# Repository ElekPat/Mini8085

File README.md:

This is my Kicad version of http://www.malinov.com/Home/sergeys-projects/minimax8085, I called it V1.1.

MAX232 and DS1210 have been removed.
Added a 6 pin header for FTDI like external USB to serial adapter.

A prototype 2.54mm pitch zone was created (pads only on bottom face). You can see it populated here with a PIC16 acting as an I2C Master controller for the 8085 (requires changes to the original MiniMax8085 GAL).

For assembling source files, I use http://john.ccac.rwth-aachen.de:8000/as/ (Macro Assembler compatible with multiple target CPUs, see my other projects)

Use the following 2 command lines to generate a HEX file:
 - asw.exe -cpu 8085 -L source.asm
 - p2hex.exe source.p -k -F Intel

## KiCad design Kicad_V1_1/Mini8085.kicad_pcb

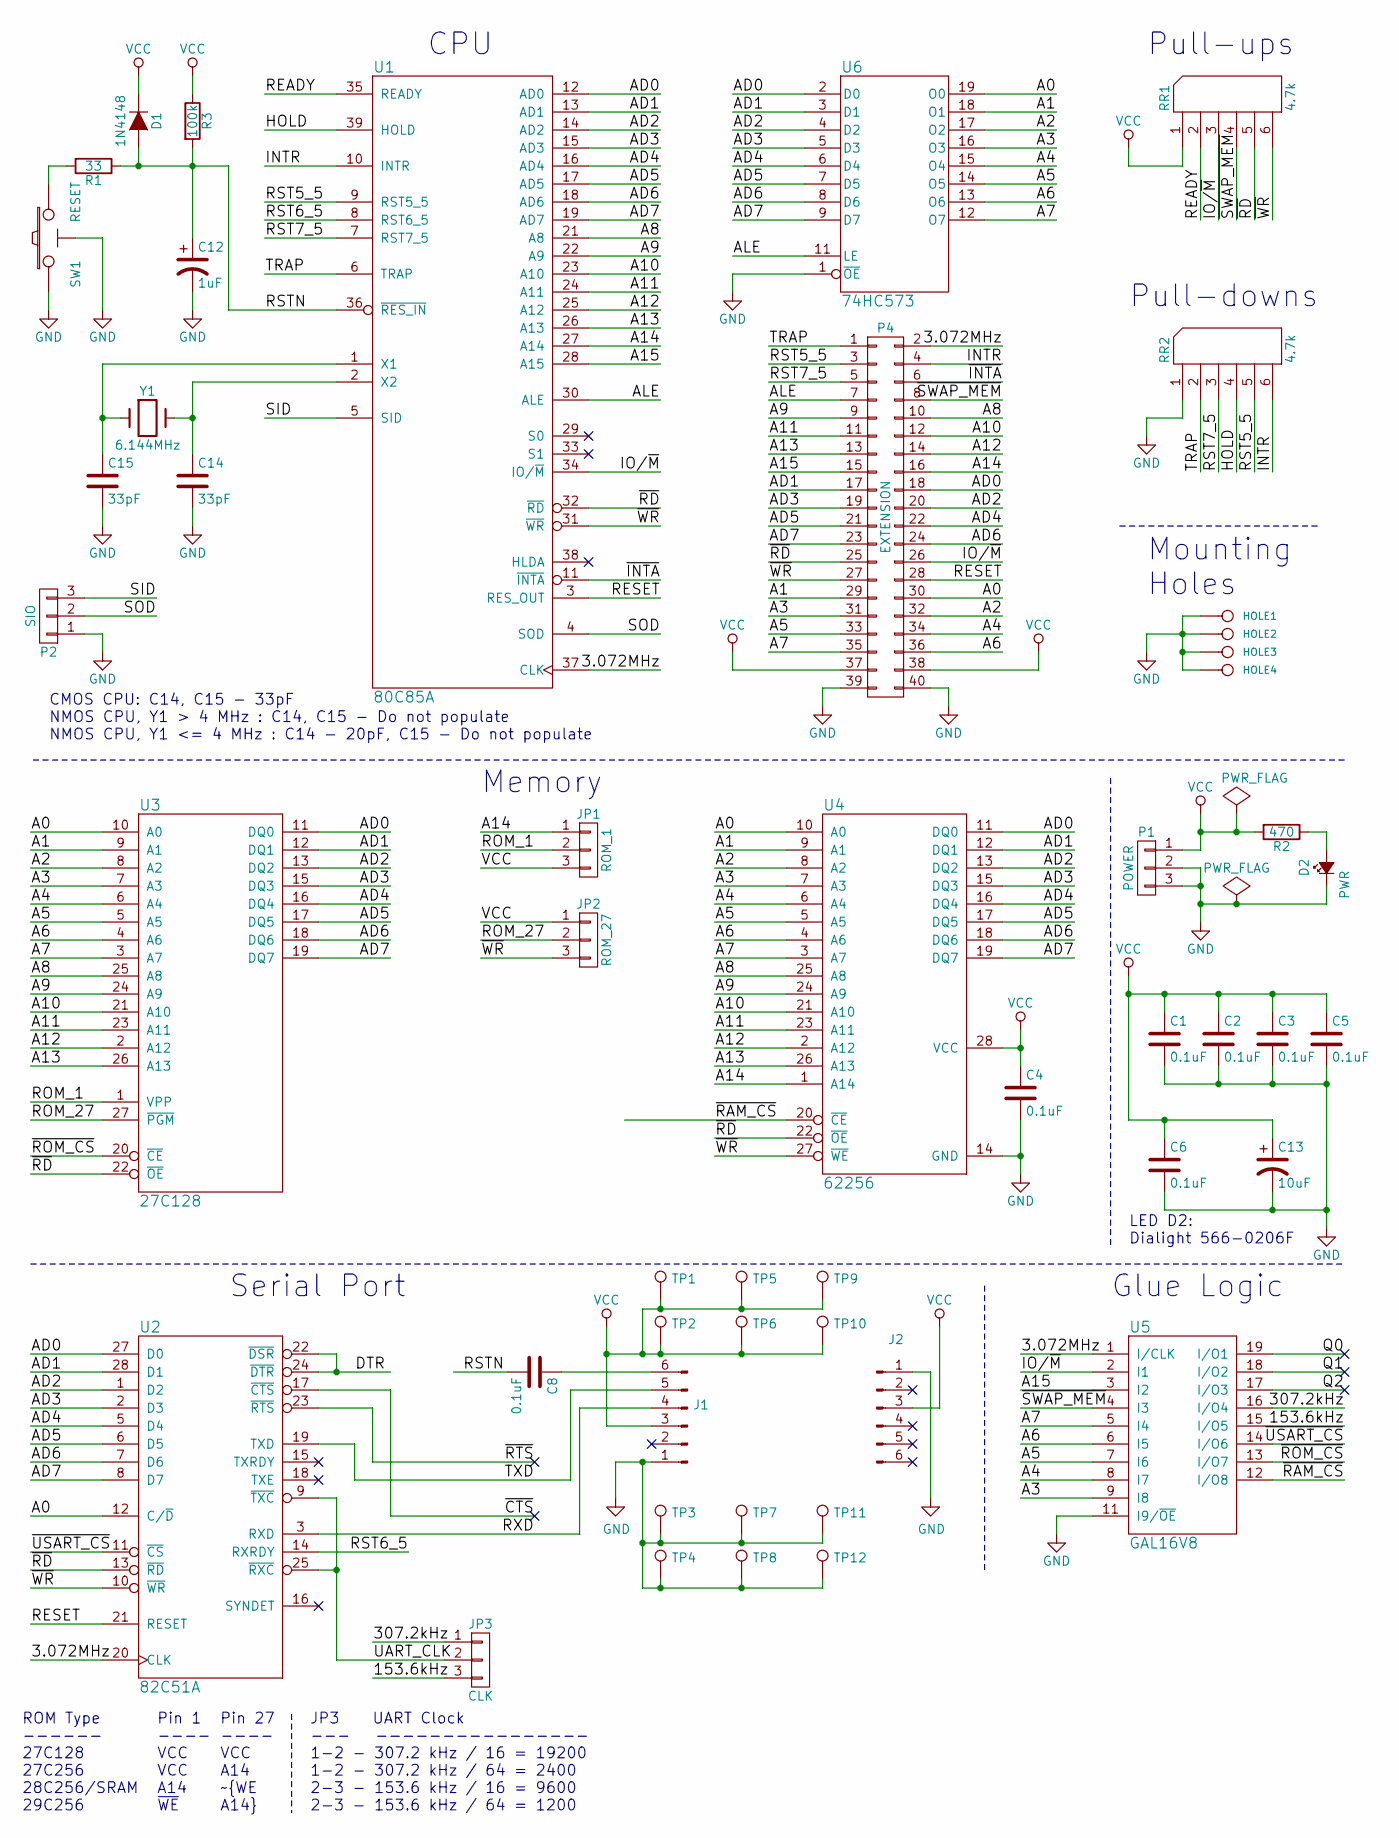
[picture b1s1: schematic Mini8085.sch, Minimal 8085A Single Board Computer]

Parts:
C1, C2, C3, C4, C5, C6: 0.1uF; Cap_Cer_508
C8: 0.1uF; C_Rect_L4.6mm_W2.0mm_P2.50mm_MKS02_FKP02
C12: 1uF; Cap_Pol_508_3
C13: 10uF; Cap_Pol_508_3
C14, C15: 33pF; Cap_Cer_508
D1: 1N4148; Diode_762
D2: PWR; LED_Dialight_566-0206F
HOLE1, HOLE2, HOLE3, HOLE4: CONN_1; Hole_3mm
J1, J2: Conn_01x06_Male; PinHeader_1x06_P2.54mm_Vertical
JP1: ROM_1; Conn_Pin_Header_3x1_2.54mm
JP2: ROM_27; Conn_Pin_Header_3x1_2.54mm
JP3: CLK; Conn_Pin_Header_3x1_2.54mm
P1: POWER; Conn_Power_Jack_Circular_Pads
P2: SIO; Conn_Pin_Header_3x1_2.54mm
P4: EXTENSION; Conn_Pin_Header_20x2_2.54mm
R1: 33; Res_762
R2: 470; Res_762
R3: 100k; Res_762
RR1, RR2: 4.7k; Conn_SIL6
SW1: RESET; Switch_Tactile_6mm_Right
TP1, TP2, TP3, TP4, TP5, TP6, TP7, TP8, TP9, TP10, TP11, TP12: TestPoint; TestPoint_THTPad_2.0x2.0mm_Drill1.0mm
U1: 80C85A; IC_DIP40_600
U2: 82C51A; IC_DIP28_600
U3: 27C128; IC_DIP28_600
U4: 62256; IC_DIP28_600
U5: GAL16V8; IC_DIP20_300
U6: 74HC573; IC_DIP20_300
Y1: 6.144MHz; Crystal_HC-49U_Vert

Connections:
/3.072MHz: P4.2, U1.37 (CLK), U2.20 (CLK), U5.1 (I/CLK)
/153.6kHz: JP3.3, U5.15 (I/O5)
/307.2kHz: JP3.1, U5.16 (I/O4)
/A0: P4.30, U2.12 (C/~D), U3.10 (A0), U4.10 (A0), U6.19 (O0)
/A1: P4.29, U3.9 (A1), U4.9 (A1), U6.18 (O1)
/A2: P4.32, U3.8 (A2), U4.8 (A2), U6.17 (O2)
/A3: P4.31, U3.7 (A3), U4.7 (A3), U5.9 (I8), U6.16 (O3)
/A4: P4.34, U3.6 (A4), U4.6 (A4), U5.8 (I7), U6.15 (O4)
/A5: P4.33, U3.5 (A5), U4.5 (A5), U5.7 (I6), U6.14 (O5)
/A6: P4.36, U3.4 (A6), U4.4 (A6), U5.6 (I5), U6.13 (O6)
/A7: P4.35, U3.3 (A7), U4.3 (A7), U5.5 (I4), U6.12 (O7)
/A8: P4.10, U1.21 (A8), U3.25 (A8), U4.25 (A8)
/A9: P4.9, U1.22 (A9), U3.24 (A9), U4.24 (A9)
/A10: P4.12, U1.23 (A10), U3.21 (A10), U4.21 (A10)
/A11: P4.11, U1.24 (A11), U3.23 (A11), U4.23 (A11)
/A12: P4.14, U1.25 (A12), U3.2 (A12), U4.2 (A12)
/A13: P4.13, U1.26 (A13), U3.26 (A13), U4.26 (A13)
/A14: JP1.1, P4.16, U1.27 (A14), U4.1 (A14)
/A15: P4.15, U1.28 (A15), U5.3 (I2)
/AD0: P4.18, U1.12 (AD0), U2.27 (D0), U3.11 (DQ0), U4.11 (DQ0), U6.2 (D0)
/AD1: P4.17, U1.13 (AD1), U2.28 (D1), U3.12 (DQ1), U4.12 (DQ1), U6.3 (D1)
/AD2: P4.20, U1.14 (AD2), U2.1 (D2), U3.13 (DQ2), U4.13 (DQ2), U6.4 (D2)
/AD3: P4.19, U1.15 (AD3), U2.2 (D3), U3.15 (DQ3), U4.15 (DQ3), U6.5 (D3)
/AD4: P4.22, U1.16 (AD4), U2.5 (D4), U3.16 (DQ4), U4.16 (DQ4), U6.6 (D4)
/AD5: P4.21, U1.17 (AD5), U2.6 (D5), U3.17 (DQ5), U4.17 (DQ5), U6.7 (D5)
/AD6: P4.24, U1.18 (AD6), U2.7 (D6), U3.18 (DQ6), U4.18 (DQ6), U6.8 (D6)
/AD7: P4.23, U1.19 (AD7), U2.8 (D7), U3.19 (DQ7), U4.19 (DQ7), U6.9 (D7)
/ALE: P4.7, U1.30 (ALE), U6.11 (LE)
/DTR: U2.22 (~DSR), U2.24 (~DTR)
/HOLD: RR2.4, U1.39 (HOLD)
/INTR: P4.4, RR2.6, U1.10 (INTR)
/IO/~M: P4.26, RR1.3, U1.34 (IO/~M), U5.2 (I1)
/Q0: U5.19 (I/O1)
/Q1: U5.18 (I/O2)
/Q2: U5.17 (I/O3)
/READY: RR1.2, U1.35 (READY)
/RESET: P4.28, U1.3 (RES_OUT), U2.21 (RESET)
/ROM_1: JP1.2, U3.1 (VPP)
/ROM_27: JP2.2, U3.27 (~PGM)
/RST5_5: P4.3, RR2.5, U1.9 (RST5_5)
/RST6_5: U1.8 (RST6_5), U2.14 (RXRDY)
/RST7_5: P4.5, RR2.3, U1.7 (RST7_5)
/RSTN: C8.2, C12.1, D1.2 (A), R1.1, R3.2, U1.36 (~RES_IN)
/RXD: J1.4, U2.3 (RXD)
/SID: P2.3, U1.5 (SID)
/SOD: P2.2, U1.4 (SOD)
/TRAP: P4.1, RR2.2, U1.6 (TRAP)
/TXD: J1.5, U2.19 (TXD)
/UART_CLK: JP3.2, U2.9 (~TXC), U2.25 (~RXC)
/~CTS: U2.17 (~CTS)
/~INTA: P4.6, U1.11 (~INTA)
/~RAM_CS: U4.20 (~CE), U5.12 (I/O8)
/~RD: P4.25, RR1.5, U1.32 (~RD), U2.13 (~RD), U3.22 (~OE), U4.22 (~OE)
/~ROM_CS: U3.20 (~CE), U5.13 (I/O7)
/~RTS: U2.23 (~RTS)
/~SWAP_MEM: P4.8, RR1.4, U5.4 (I3)
/~USART_CS: U2.11 (~CS), U5.14 (I/O6)
/~WR: JP2.3, P4.27, RR1.6, U1.31 (~WR), U2.10 (~WR), U4.27 (~WE)
GND: C1.2, C2.2, C3.2, C4.2, C5.2, C6.2, C12.2, C13.2, C14.2, C15.2, D2.1 (K), HOLE1.1, HOLE2.1, HOLE3.1, HOLE4.1, J1.1, J2.1, P1.2, P1.3, P2.1, P4.39, P4.40, RR2.1 (COM), SW1.1, SW1.GND, TP3.1, TP4.1, TP7.1, TP8.1, TP11.1, TP12.1, U1.20 (GND), U2.4 (GND), U3.14 (GND), U4.14 (GND), U5.10 (GND), U5.11 (I9/~OE), U6.1 (~OE), U6.10 (GND)
unnamed: C8.1, J1.6
unnamed: C14.1, U1.2 (X2), Y1.2
unnamed: C15.1, U1.1 (X1), Y1.1
unnamed: D2.2 (A), R2.1
unnamed: R1.2, SW1.2
VCC: C1.1, C2.1, C3.1, C4.1, C5.1, C6.1, C13.1, D1.1 (K), J1.3, J2.3, JP1.3, JP2.1, P1.1, P4.37, P4.38, R2.2, R3.1, RR1.1 (COM), TP1.1, TP2.1, TP5.1, TP6.1, TP9.1, TP10.1, U1.40 (VCC), U2.26 (VCC), U3.28 (VCC), U4.28 (VCC), U5.20 (VCC), U6.20 (VCC)

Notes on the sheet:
ROM Type ------ 27C128 27C256 28C256/SRAM 29C256
CMOS CPU: C14, C15 - 33pF NMOS CPU, Y1 > 4 MHz : C14, C15 - Do not populate NMOS CPU, Y1 <= 4 MHz : C14 - 20pF, C15 - Do not populate
Memory
Serial Port
CPU
Pull-downs
Mounting Holes
LED D2: Dialight 566-0206F
Glue Logic
Pull-ups
JP3 UART Clock --- ---------------- 1-2 - 307.2 kHz / 16 = 19200 1-2 - 307.2 kHz / 64 = 2400 2-3 - 153.6 kHz / 16 = 9600 2-3 - 153.6 kHz / 64 = 1200
Pin 1 ---- VCC VCC A14 ~WE
Pin 27 ---- VCC A14 ~WE A14

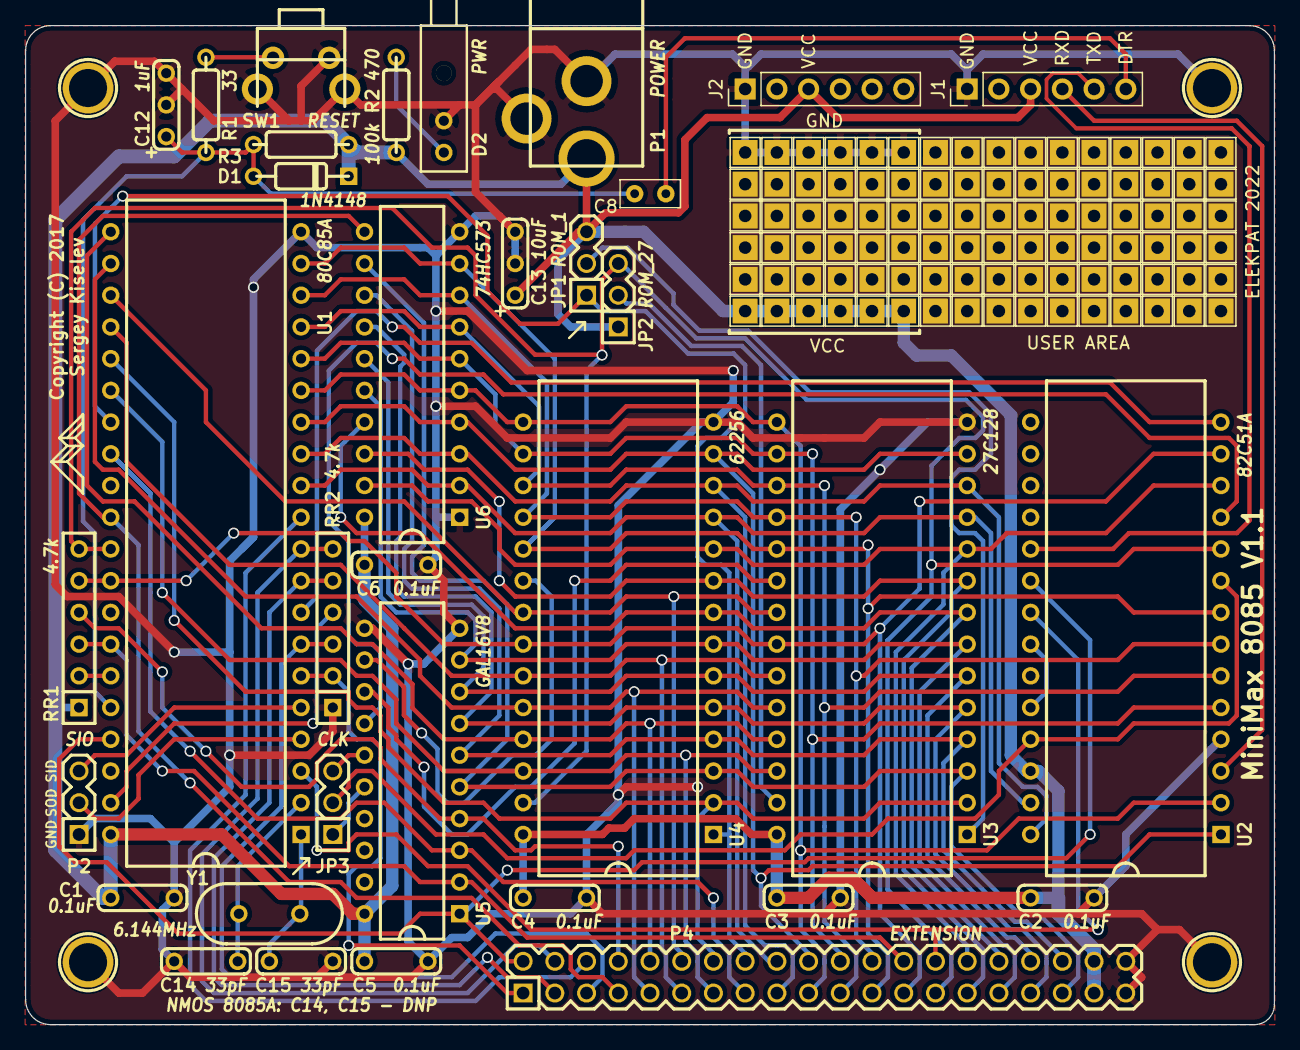
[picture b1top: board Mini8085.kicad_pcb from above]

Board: 2 copper layers, 100.0 x 80.0 mm, 50 parts (0 on the bottom side), 60 nets.

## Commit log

2023-04-11 Add pictures via Upload
2023-04-11 Add Kicad files
2023-04-11 Add Schematics in PDF format

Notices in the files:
Kicad_V1_1/Mini8085.kicad_pcb:
Copyright (C) 2017
